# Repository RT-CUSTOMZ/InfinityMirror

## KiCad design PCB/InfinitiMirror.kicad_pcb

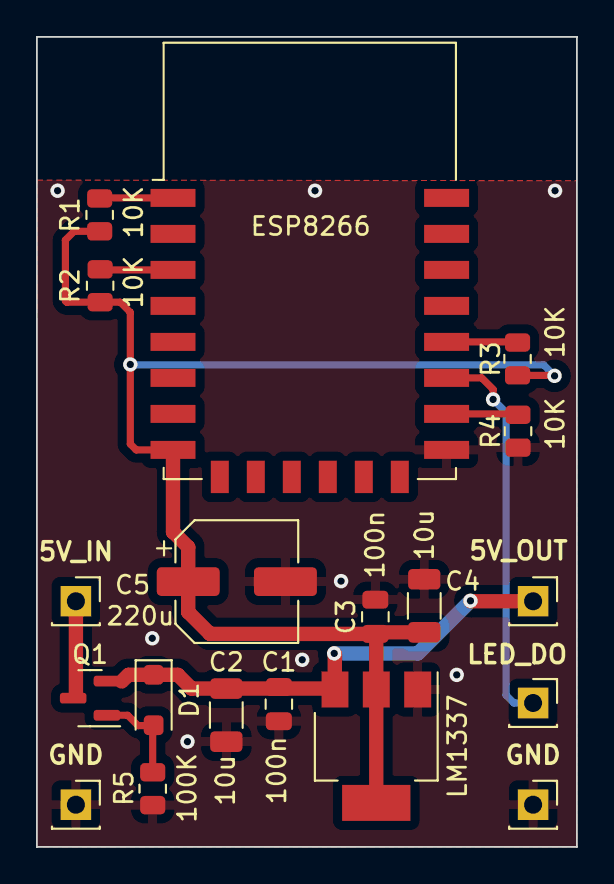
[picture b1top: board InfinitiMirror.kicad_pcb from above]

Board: 2 copper layers, 30.0 x 45.0 mm, 19 parts (0 on the bottom side), 10 nets.

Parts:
5V_IN: 5V_In; PinSocket_1x01_P2.54mm_Vertical
5V_OUT: 5V; PinSocket_1x01_P2.54mm_Vertical
C1, C3: 100nF; C_0805_2012Metric
C2, C4: 10u; C_1206_3216Metric
C5: 330u; CP_Elec_6.3x7.7
D1: BZT52C6V8; D_SOD-123F
ESP8266: ESP-12F; ESP-12E
GND: Ground; PinSocket_1x01_P2.54mm_Vertical
GND#2: Ground; PinSocket_1x01_P2.54mm_Vertical
LED_DO: LED_DATA; PinSocket_1x01_P2.54mm_Vertical
LM1337: LT1117-3.3; SOT-223-3_TabPin2
Q1: FDN340P; SOT-23
R1, R2, R3, R4: 10k; R_0805_2012Metric
R5: 100k; R_0805_2012Metric

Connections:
+5V: 5V_OUT.1, C1.1, C2.1, D1.1 (K), LM1337.3 (VI), Q1.2 (S)
GND: C1.2, C2.2, C3.2, C4.2, C5.2, ESP8266.15 (GND), GND.1, GND#2.1, LM1337.1 (GND), R4.2, R5.2
unnamed: D1.2 (A), Q1.1 (G), R5.1
unnamed: 5V_IN.1, Q1.3 (D)
unnamed: ESP8266.17 (GPIO2), LED_DO.1
unnamed: ESP8266.3 (EN), R2.2
unnamed: ESP8266.18 (GPIO0), R3.2
unnamed: ESP8266.16 (GPIO15), R4.1
unnamed: C3.1, C4.1, C5.1, ESP8266.8 (VCC), LM1337.2 (VO), R1.1, R2.1, R3.1
unnamed: ESP8266.1 (~RST), R1.2

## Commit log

2023-08-31 Create blah
2023-08-31 Gerber Data for JLC Order
    Panalized
    6 PCBs per Panel
2023-08-31 Version mit FH Logo und 30 LED
2023-08-31 Version für 30 LED
2023-09-18 Schaltplan hinzugefügt
2023-09-28 DC Buchse geändert
2023-09-28 Adapterblende
    Adapterblende für neue DC Buchse, damit diese weniger weit hervorsteht.
